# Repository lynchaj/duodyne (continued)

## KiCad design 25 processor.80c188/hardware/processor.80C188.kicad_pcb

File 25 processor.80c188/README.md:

# Duodyne 80c188 Card
80c188 processor board (hardware and software) for the Duodyne computer system.

Based on the Retrobew Computer SBC-188 board by John Coffman

## Firmware

### BIOS
 The firmware in the BIOS folder is a subset of the SBC-188 firmware.   It currently runs MS-DOS 3.3 and supports PPIDE drives on the Duodyne Disk IO card and USB drives on the Multi IO card.  It requires a RAMROM card and can be used as a primary or secondary CPU.   The RAMROM RTC is supported.
 
 UART must be jumpered for EIRQ0
 
#### BIOS ToDo:
* DiskIO Floppy Drive Support
* Missing Disk-io SD Support
* Missing Disk-io Network Support
* BIOS Support for the PCF 8584
* Better Front Panel Support
* Test multi-io serial support 
* Support for other DuoDyne Hardware
 1.Voice
 1.DualESP
 1.MappedVideo
* Support for Xenix 86
* Support for CPM 86

### Monitor
This is a simple monitor "Mon88" originally by Hans Tiggeler - http://www.ht-lab.com

### Test Programs
There are also two test roms provided.  
* Scream -- this program outputs a constant stream of "A" at 9600-n-8-1 via the on-board uart.
* Scram -- this program outputs an incrimenting character from a RAM address at 9600-n-8-1 via the on-board uart.

## Bugs 
### Hardware
   1. V 0.70
   * To get RAM access -- A21 needs to be high, and it is not. Also A20 should not be left floating.   
      1.  Connect P2 Pin 26 to U17 Pin 18.
      1.  Connect P2 Pin 28 to U17 Pin 16.
      1.  Connect RN1 Pin 3 to U17 Pin 2.
      1.  Connect RN1 Pin 5 to U17 Pin 4.
      1.  Cut Trace between U17 Pin 1 and Pin 19 (bottom of board)
      1.  Connect U17 Pin 1 U6 Pin 19

### BIOS
* Missing multi-io Mouse Support (no plans to support)
* Missing multi-io SD Support (no plans to support)

## Jumper Settings (V.90)

      JP1  - Allow RES_IN to generate board Reset
      
      JP4 - Pullups for IORQ,MREQ,WR,RD.   
            All Open for Secondary CPU
            All Shorted for only CPU

      J1 - Activation Address Port
        
      J2  - CPU Control
                1&2 Only CPU
                2&3 Secondary CPU
      
      J3  - Reset Control
                1&2 Only CPU
                2&3 Secondary CPU                
      
      J4 - Reset Switch Input
        
      J5 - Bus IRQ Enable (0-3)
                1&2 Enable Bus EIRQ3 to Int3
                3&4 Enable Bus EIRQ2 to Int2
                5&6 Enable Bus EIRQ1 to Int1
                7&8 Enable Bus EIRQ0 to Int0

      J7 i2c IRQ Selection
        
      J8 UART IRQ Selection
            (BIOS Requires INT0 - tbd)

      J13 Rom Type Selection
            1&2 32 pin Flash or CMOS 
            2&3 28 pin Flash or CMOS 
        
      J14 Rom Type Selection
            1&2 Flash (not Write Protected)
            2&3 CMOS (512K)

## BOM (V0.90)      
Qty|Reference(s)|Value
--- | ----------- | -----
33|C2, C3, C4, C5, C6, C8, C9, C10, C11, C12, C13, C14, C15, C16, C17, C18, C19, C20, C21, C22, C23, C24, C30, C31, C32, C33, C34, C35, C36, C37, C38, C39, C40|0.1u
4|C25, C26, C27, C28|10u Electrolytic
1|C29|22u Electrolytic
1|C46|47uF Electrolytic
8|D2, D5, D7, D8, D9, D10, D11, D12|LED
1|D4|LED
1|D6|1N4148
1|J1|Pin Header 02x08
1|J2|Pin Header 01x03
1|J3|Pin Header 01x03
1|J4|Pin Header 01x02
1|J7|Pin Header 02x09
1|J8|Pin Header 02x09
1|J11|Pin Header 02x20
2|J13, J14|Pin Header 01x03
1|JP1|Pin Header  01x02
1|JP4|Pin Header 02x04
3|P1, P2, P3|Pin Header 02x25
3|R1, R2, R3|10K
3|R4, R6, R7|1K
1|R5|10
1|R9|1K
3|RN1, RN4, RN5|4700  8 res network
1|RN2|10K  8 res network
1|RN3|470 8 res network
1|RN6|470 4 res network 
1|SW1|Switch:SW_Push
1|U1|74LS04
1|U2|74LS32
2|U3, U19|74ALS373
1|U4|74LS07
1|U5|8259
6|U6, U8, U10, U14, U17, U31|74LS244
1|U7|74LS240
1|U9|OSC 2x rated CPU freq (10-20mhz, should be an even number)
1|U11|74LS245
1|U12|80C188
1|U13|DS1233
2|U15, U25|GAL22V10
1|U16|74LS08
1|U18|OSC 1.8432
1|U20|TL16C550CFN
1|U21|74LS74
1|U22|74LS688
1|U23|74LS00
1|U24|74LS259
1|U26|29F040
1|U27|PCF8584
1|U28|PCF CLOCK
1|U33|74LS374

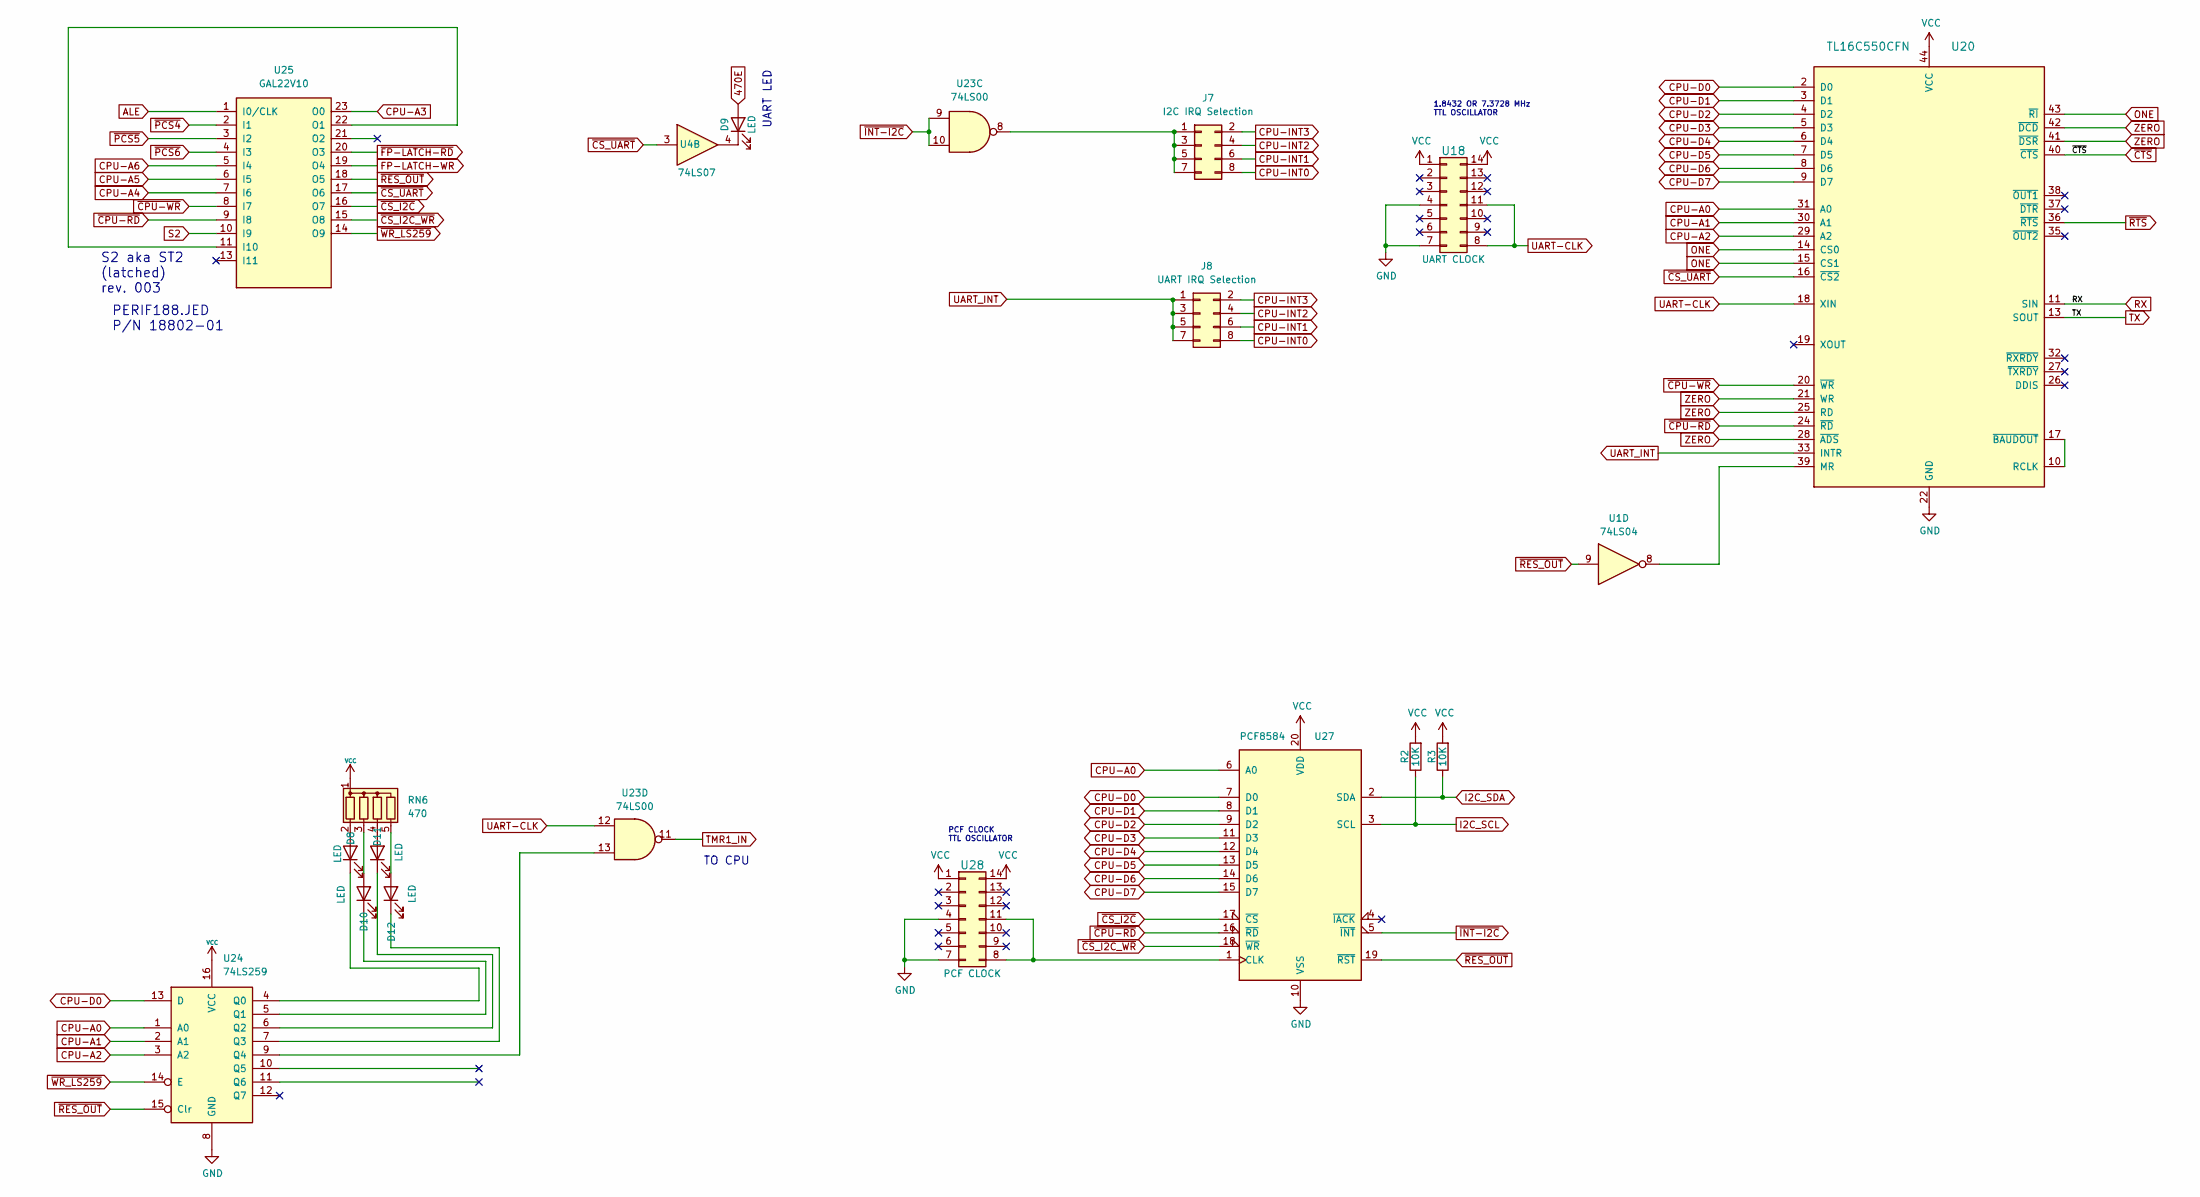
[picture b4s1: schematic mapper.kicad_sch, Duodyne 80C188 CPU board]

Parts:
D8, D9, D10, D11, D12: LED; LED_D3.0mm_Horizontal_O3.81mm_Z2.0mm
J7: I2C IRQ Selection; PinHeader_2x04_P2.54mm_Vertical
J8: UART IRQ Selection; PinHeader_2x04_P2.54mm_Vertical
R2, R3: 10K; R_Axial_DIN0207_L6.3mm_D2.5mm_P7.62mm_Horizontal
RN6: 470; R_Array_SIP5
U1: 74LS04; DIP-14_W7.62mm_Socket_LongPads
U4: 74LS07; DIP-14_W7.62mm_Socket_LongPads
U18: UART CLOCK; DIP-14_W7.62mm_Socket_LongPads
U20: TL16C550CFN; PLCC-44_THT-Socket
U23: 74LS00; DIP-14_W7.62mm_Socket_LongPads
U24: 74LS259; DIP-16_W7.62mm_Socket_LongPads
U25: GAL22V10; DIP-24_W7.62mm_Socket_LongPads
U27: PCF8584; DIP-20_W7.62mm_Socket_LongPads
U28: PCF CLOCK; DIP-14_W7.62mm_Socket_LongPads

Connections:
470E: D9.2 (A); also elsewhere on the board
ALE: U25.1 (I0/CLK); also elsewhere on the board
CPU-A0: U20.31 (A0), U24.1 (A0), U27.6 (A0); also elsewhere on the board
CPU-A1: U20.30 (A1), U24.2 (A1); also elsewhere on the board
CPU-A2: U20.29 (A2), U24.3 (A2); also elsewhere on the board
CPU-A3: U25.23 (O0); also elsewhere on the board
CPU-A4: U25.7 (I6); also elsewhere on the board
CPU-A5: U25.6 (I5); also elsewhere on the board
CPU-A6: U25.5 (I4); also elsewhere on the board
CPU-D0: U20.2 (D0), U24.13 (D), U27.7 (D0); also elsewhere on the board
CPU-D1: U20.3 (D1), U27.8 (D1); also elsewhere on the board
CPU-D2: U20.4 (D2), U27.9 (D2); also elsewhere on the board
CPU-D3: U20.5 (D3), U27.11 (D3); also elsewhere on the board
CPU-D4: U20.6 (D4), U27.12 (D4); also elsewhere on the board
CPU-D5: U20.7 (D5), U27.13 (D5); also elsewhere on the board
CPU-D6: U20.8 (D6), U27.14 (D6); also elsewhere on the board
CPU-D7: U20.9 (D7), U27.15 (D7); also elsewhere on the board
CPU-INT0: J7.8, J8.8; also elsewhere on the board
CPU-INT1: J7.6, J8.6; also elsewhere on the board
CPU-INT2: J7.4, J8.4; also elsewhere on the board
CPU-INT3: J7.2, J8.2; also elsewhere on the board
FP-LATCH-WR: U25.19 (O4); also elsewhere on the board
GND: U18.4, U18.7, U20.22 (GND), U24.8 (GND), U25.12 (GND), U27.10 (VSS), U28.4, U28.7; also elsewhere on the board
I2C_SCL: R2.1, U27.3 (SCL); also elsewhere on the board
I2C_SDA: R3.1, U27.2 (SDA); also elsewhere on the board
unnamed: D8.1 (K), U24.4 (Q0)
unnamed: D8.2 (A), RN6.2 (R1)
unnamed: D9.1 (K), U4.4
unnamed: D10.1 (K), U24.5 (Q1)
unnamed: D10.2 (A), RN6.3 (R2)
unnamed: D11.1 (K), U24.6 (Q2)
unnamed: D11.2 (A), RN6.4 (R3)
unnamed: D12.1 (K), U24.7 (Q3)
unnamed: D12.2 (A), RN6.5 (R4)
unnamed: J7.1, J7.3, J7.5, J7.7, U23.8
unnamed: U1.8, U20.39 (MR)
unnamed: U20.10 (RCLK), U20.17 (~BAUDOUT)
unnamed: U23.13, U24.9 (Q4)
unnamed: U25.11 (I10), U25.22 (O1)
unnamed: U27.1 (CLK), U28.8, U28.11
ONE: U20.14 (CS0), U20.15 (CS1), U20.43 (~RI); also elsewhere on the board
RX: U20.11 (SIN); also elsewhere on the board
S2: U25.10 (I9); also elsewhere on the board
TMR1_IN: U23.11; also elsewhere on the board
TX: U20.13 (SOUT); also elsewhere on the board
UART-CLK: U18.8, U18.11, U20.18 (XIN), U23.12
UART_INT: J8.1, J8.3, J8.5, J8.7, U20.33 (INTR)
VCC: R2.2, R3.2, RN6.1 (common), U18.1, U18.14, U20.44 (VCC), U24.16 (VCC), U25.24 (VCC), U27.20 (VDD), U28.1, U28.14; also elsewhere on the board
ZERO: U20.21 (WR), U20.25 (RD), U20.28 (~ADS), U20.41 (~DSR), U20.42 (~DCD); also elsewhere on the board
~CPU-RD: U20.24 (~RD), U25.9 (I8), U27.16 (~RD); also elsewhere on the board
~CPU-WR: U20.20 (~WR), U25.8 (I7); also elsewhere on the board
~CS_I2C_WR: U25.15 (O8), U27.18 (~WR)
~CS_I2C: U25.16 (O7), U27.17 (~CS)
~CS_UART: U4.3, U20.16 (~CS2), U25.17 (O6)
~CTS: U20.40 (~CTS); also elsewhere on the board
~FP-LATCH-RD: U25.20 (O3); also elsewhere on the board
~INT-I2C: U23.9, U23.10, U27.5 (~INT)
~PCS4: U25.2 (I1); also elsewhere on the board
~PCS5: U25.3 (I2); also elsewhere on the board
~PCS6: U25.4 (I3); also elsewhere on the board
~RES_OUT: U1.9, U24.15 (Clr), U25.18 (O5), U27.19 (~RST); also elsewhere on the board
~RTS: U20.36 (~RTS); also elsewhere on the board
~WR_LS259: U24.14 (E), U25.14 (O9)

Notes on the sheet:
PERIF188.JED P/N 18802-01
TO CPU
PCF CLOCK TTL OSCILLATOR
UART LED
S2 aka ST2 (latched) rev. 003
1.8432 OR 7.3728 MHz TTL OSCILLATOR

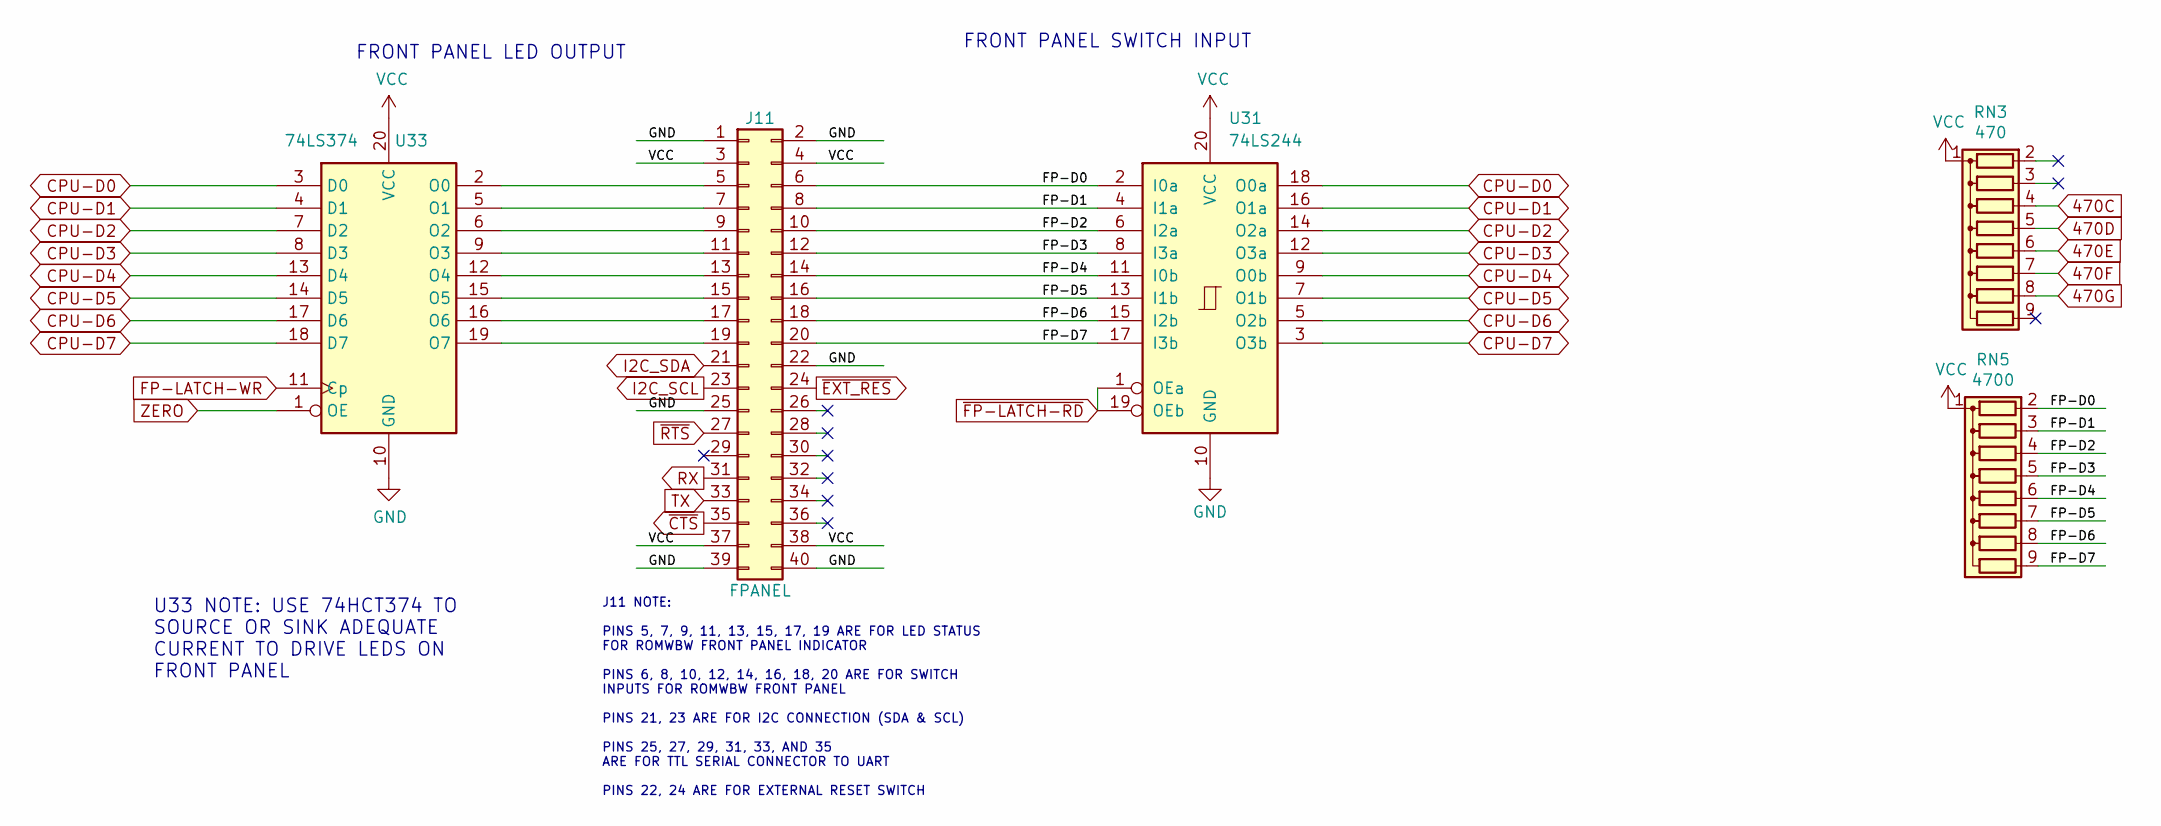
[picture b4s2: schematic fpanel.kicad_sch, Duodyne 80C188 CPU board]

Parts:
J11: FPANEL; IDC-Header_2x20_P2.54mm_Horizontal
RN3: 470; R_Array_SIP9
RN5: 4700; R_Array_SIP9
U31: 74LS244; DIP-20_W7.62mm_Socket_LongPads
U33: 74LS374; DIP-20_W7.62mm_Socket_LongPads

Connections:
470C: RN3.4 (R3); also elsewhere on the board
470D: RN3.5 (R4); also elsewhere on the board
470E: RN3.6 (R5); also elsewhere on the board
470F: RN3.7 (R6); also elsewhere on the board
470G: RN3.8 (R7); also elsewhere on the board
/fpanel/FP-D0: J11.6, RN5.2 (R1), U31.2 (I0a)
/fpanel/FP-D1: J11.8, RN5.3 (R2), U31.4 (I1a)
/fpanel/FP-D2: J11.10, RN5.4 (R3), U31.6 (I2a)
/fpanel/FP-D3: J11.12, RN5.5 (R4), U31.8 (I3a)
/fpanel/FP-D4: J11.14, RN5.6 (R5), U31.11 (I0b)
/fpanel/FP-D5: J11.16, RN5.7 (R6), U31.13 (I1b)
/fpanel/FP-D6: J11.18, RN5.8 (R7), U31.15 (I2b)
/fpanel/FP-D7: J11.20, RN5.9 (R8), U31.17 (I3b)
CPU-D0: U31.18 (O0a), U33.3 (D0); also elsewhere on the board
CPU-D1: U31.16 (O1a), U33.4 (D1); also elsewhere on the board
CPU-D2: U31.14 (O2a), U33.7 (D2); also elsewhere on the board
CPU-D3: U31.12 (O3a), U33.8 (D3); also elsewhere on the board
CPU-D4: U31.9 (O0b), U33.13 (D4); also elsewhere on the board
CPU-D5: U31.7 (O1b), U33.14 (D5); also elsewhere on the board
CPU-D6: U31.5 (O2b), U33.17 (D6); also elsewhere on the board
CPU-D7: U31.3 (O3b), U33.18 (D7); also elsewhere on the board
FP-LATCH-WR: U33.11 (Cp); also elsewhere on the board
GND: J11.1, J11.2, J11.22, J11.25, J11.39, J11.40, U31.10 (GND), U33.10 (GND); also elsewhere on the board
I2C_SCL: J11.23; also elsewhere on the board
I2C_SDA: J11.21; also elsewhere on the board
unnamed: J11.5, U33.2 (O0)
unnamed: J11.7, U33.5 (O1)
unnamed: J11.9, U33.6 (O2)
unnamed: J11.11, U33.9 (O3)
unnamed: J11.13, U33.12 (O4)
unnamed: J11.15, U33.15 (O5)
unnamed: J11.17, U33.16 (O6)
unnamed: J11.19, U33.19 (O7)
RX: J11.31; also elsewhere on the board
TX: J11.33; also elsewhere on the board
VCC: J11.3, J11.4, J11.37, J11.38, RN3.1 (common), RN5.1 (common), U31.20 (VCC), U33.20 (VCC); also elsewhere on the board
ZERO: U33.1 (OE); also elsewhere on the board
~CTS: J11.35; also elsewhere on the board
~EXT_RES: J11.24; also elsewhere on the board
~FP-LATCH-RD: U31.1 (OEa), U31.19 (OEb); also elsewhere on the board
~RTS: J11.27; also elsewhere on the board

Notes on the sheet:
J11 NOTE: PINS 5, 7, 9, 11, 13, 15, 17, 19 ARE FOR LED STATUS FOR ROMWBW FRONT PANEL INDICATOR PINS 6, 8, 10, 12, 14, 16, 18, 20 ARE FOR SWITCH INPUTS FOR ROMWBW FRONT PANEL PINS 21, 23 ARE FOR I2C CONNECTION (SDA & SCL) PINS 25, 27, 29, 31, 33, AND 35 ARE FOR TTL SERIAL CONNECTOR TO UART PINS 22, 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
U33 NOTE: USE 74HCT374 TO SOURCE OR SINK ADEQUATE CURRENT TO DRIVE LEDS ON FRONT PANEL
FRONT PANEL SWITCH INPUT
FRONT PANEL LED OUTPUT

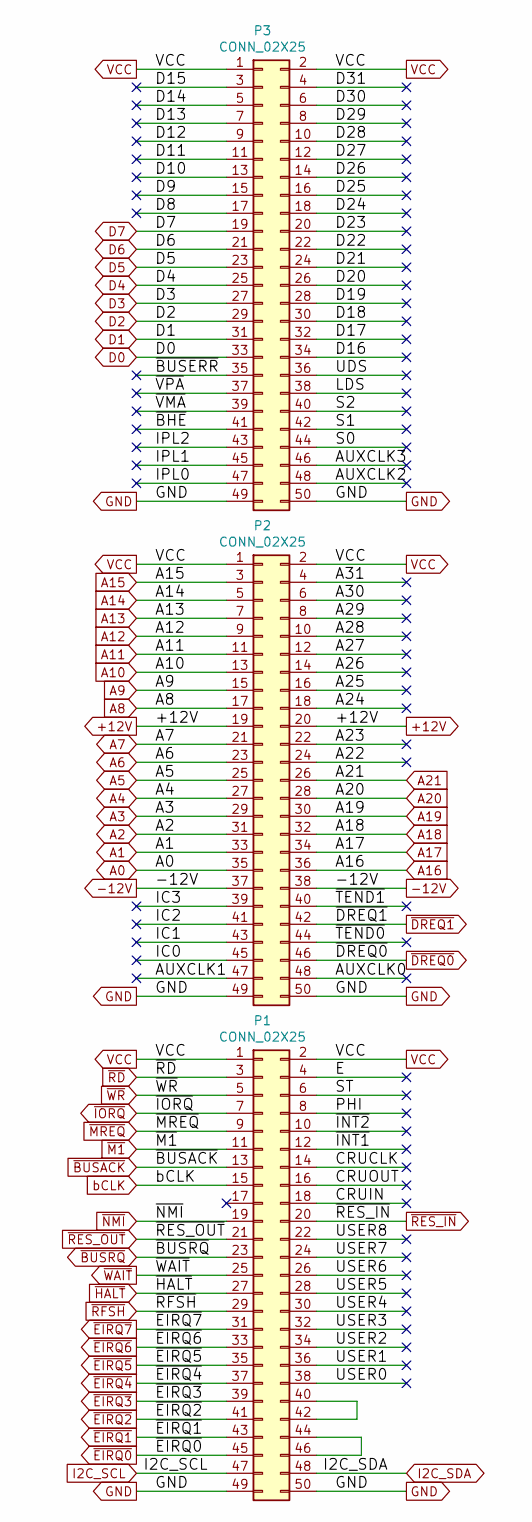
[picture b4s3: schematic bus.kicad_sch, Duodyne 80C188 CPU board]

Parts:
P1, P2, P3: CONN_02X25; IDC-Header_2x25_P2.54mm_Horizontal

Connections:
+12V: P2.19, P2.20
-12V: P2.37, P2.38
/bus/A22: P2.24
/bus/A23: P2.22
/bus/A24: P2.18
/bus/A25: P2.16
/bus/A26: P2.14
/bus/A27: P2.12
/bus/A28: P2.10
/bus/A29: P2.8
/bus/A30: P2.6
/bus/A31: P2.4
/bus/AUXCLK0: P2.48
/bus/AUXCLK1: P2.47
/bus/AUXCLK2: P3.48
/bus/AUXCLK3: P3.46
/bus/CRUCLK: P1.14
/bus/CRUIN: P1.18
/bus/CRUOUT: P1.16
/bus/D8: P3.17
/bus/D9: P3.15
/bus/D10: P3.13
/bus/D11: P3.11
/bus/D12: P3.9
/bus/D13: P3.7
/bus/D14: P3.5
/bus/D15: P3.3
/bus/D16: P3.34
/bus/D17: P3.32
/bus/D18: P3.30
/bus/D19: P3.28
/bus/D20: P3.26
/bus/D21: P3.24
/bus/D22: P3.22
/bus/D23: P3.20
/bus/D24: P3.18
/bus/D25: P3.16
/bus/D26: P3.14
/bus/D27: P3.12
/bus/D28: P3.10
/bus/D29: P3.8
/bus/D30: P3.6
/bus/D31: P3.4
/bus/E: P1.4
/bus/IC0: P2.45
/bus/IC1: P2.43
/bus/IC2: P2.41
/bus/IC3: P2.39
/bus/IPL0: P3.47
/bus/IPL1: P3.45
/bus/IPL2: P3.43
/bus/LDS: P3.38
/bus/PHI: P1.8
/bus/S0: P3.44
/bus/S1: P3.42
/bus/S2: P3.40
/bus/ST: P1.6
/bus/UDS: P3.36
/bus/USER0: P1.38
/bus/USER1: P1.36
/bus/USER2: P1.34
/bus/USER3: P1.32
/bus/USER4: P1.30
/bus/USER5: P1.28
/bus/USER6: P1.26
/bus/USER7: P1.24
/bus/USER8: P1.22
/bus/~BHE: P3.41
/bus/~BUSERR: P3.35
/bus/~INT1: P1.12
/bus/~INT2: P1.10
/bus/~TEND0: P2.44
/bus/~TEND1: P2.40
/bus/~VMA: P3.39
/bus/~VPA: P3.37
A0: P2.35; also elsewhere on the board
A1: P2.33; also elsewhere on the board
A2: P2.31; also elsewhere on the board
A3: P2.29; also elsewhere on the board
A4: P2.27; also elsewhere on the board
A5: P2.25; also elsewhere on the board
A6: P2.23; also elsewhere on the board
A7: P2.21; also elsewhere on the board
A8: P2.17; also elsewhere on the board
A9: P2.15; also elsewhere on the board
A10: P2.13; also elsewhere on the board
A11: P2.11; also elsewhere on the board
A12: P2.9; also elsewhere on the board
A13: P2.7; also elsewhere on the board
A14: P2.5; also elsewhere on the board
A15: P2.3; also elsewhere on the board
A16: P2.36; also elsewhere on the board
A17: P2.34; also elsewhere on the board
A18: P2.32; also elsewhere on the board
A19: P2.30; also elsewhere on the board
A20: P2.28; also elsewhere on the board
A21: P2.26; also elsewhere on the board
D0: P3.33; also elsewhere on the board
D1: P3.31; also elsewhere on the board
D2: P3.29; also elsewhere on the board
D3: P3.27; also elsewhere on the board
D4: P3.25; also elsewhere on the board
D5: P3.23; also elsewhere on the board
D6: P3.21; also elsewhere on the board
D7: P3.19; also elsewhere on the board
GND: P1.49, P1.50, P2.49, P2.50, P3.49, P3.50; also elsewhere on the board
I2C_SCL: P1.47; also elsewhere on the board
I2C_SDA: P1.48; also elsewhere on the board
unnamed: P1.40, P1.42
unnamed: P1.44, P1.46
VCC: P1.1, P1.2, P2.1, P2.2, P3.1, P3.2; also elsewhere on the board
bCLK: P1.15; also elsewhere on the board
~BUSACK: P1.13; also elsewhere on the board
~BUSRQ: P1.23; also elsewhere on the board
~DREQ0: P2.46; also elsewhere on the board
~DREQ1: P2.42; also elsewhere on the board
~EIRQ0: P1.45; also elsewhere on the board
~EIRQ1: P1.43; also elsewhere on the board
~EIRQ2: P1.41; also elsewhere on the board
~EIRQ3: P1.39; also elsewhere on the board
~EIRQ4: P1.37; also elsewhere on the board
~EIRQ5: P1.35; also elsewhere on the board
~EIRQ6: P1.33; also elsewhere on the board
~EIRQ7: P1.31; also elsewhere on the board
~HALT: P1.27; also elsewhere on the board
~IORQ: P1.7; also elsewhere on the board
~M1: P1.11; also elsewhere on the board
~MREQ: P1.9; also elsewhere on the board
~NMI: P1.19; also elsewhere on the board
~RD: P1.3; also elsewhere on the board
~RES_IN: P1.20; also elsewhere on the board
~RES_OUT: P1.21; also elsewhere on the board
~RFSH: P1.29; also elsewhere on the board
~WAIT: P1.25; also elsewhere on the board
~WR: P1.5; also elsewhere on the board

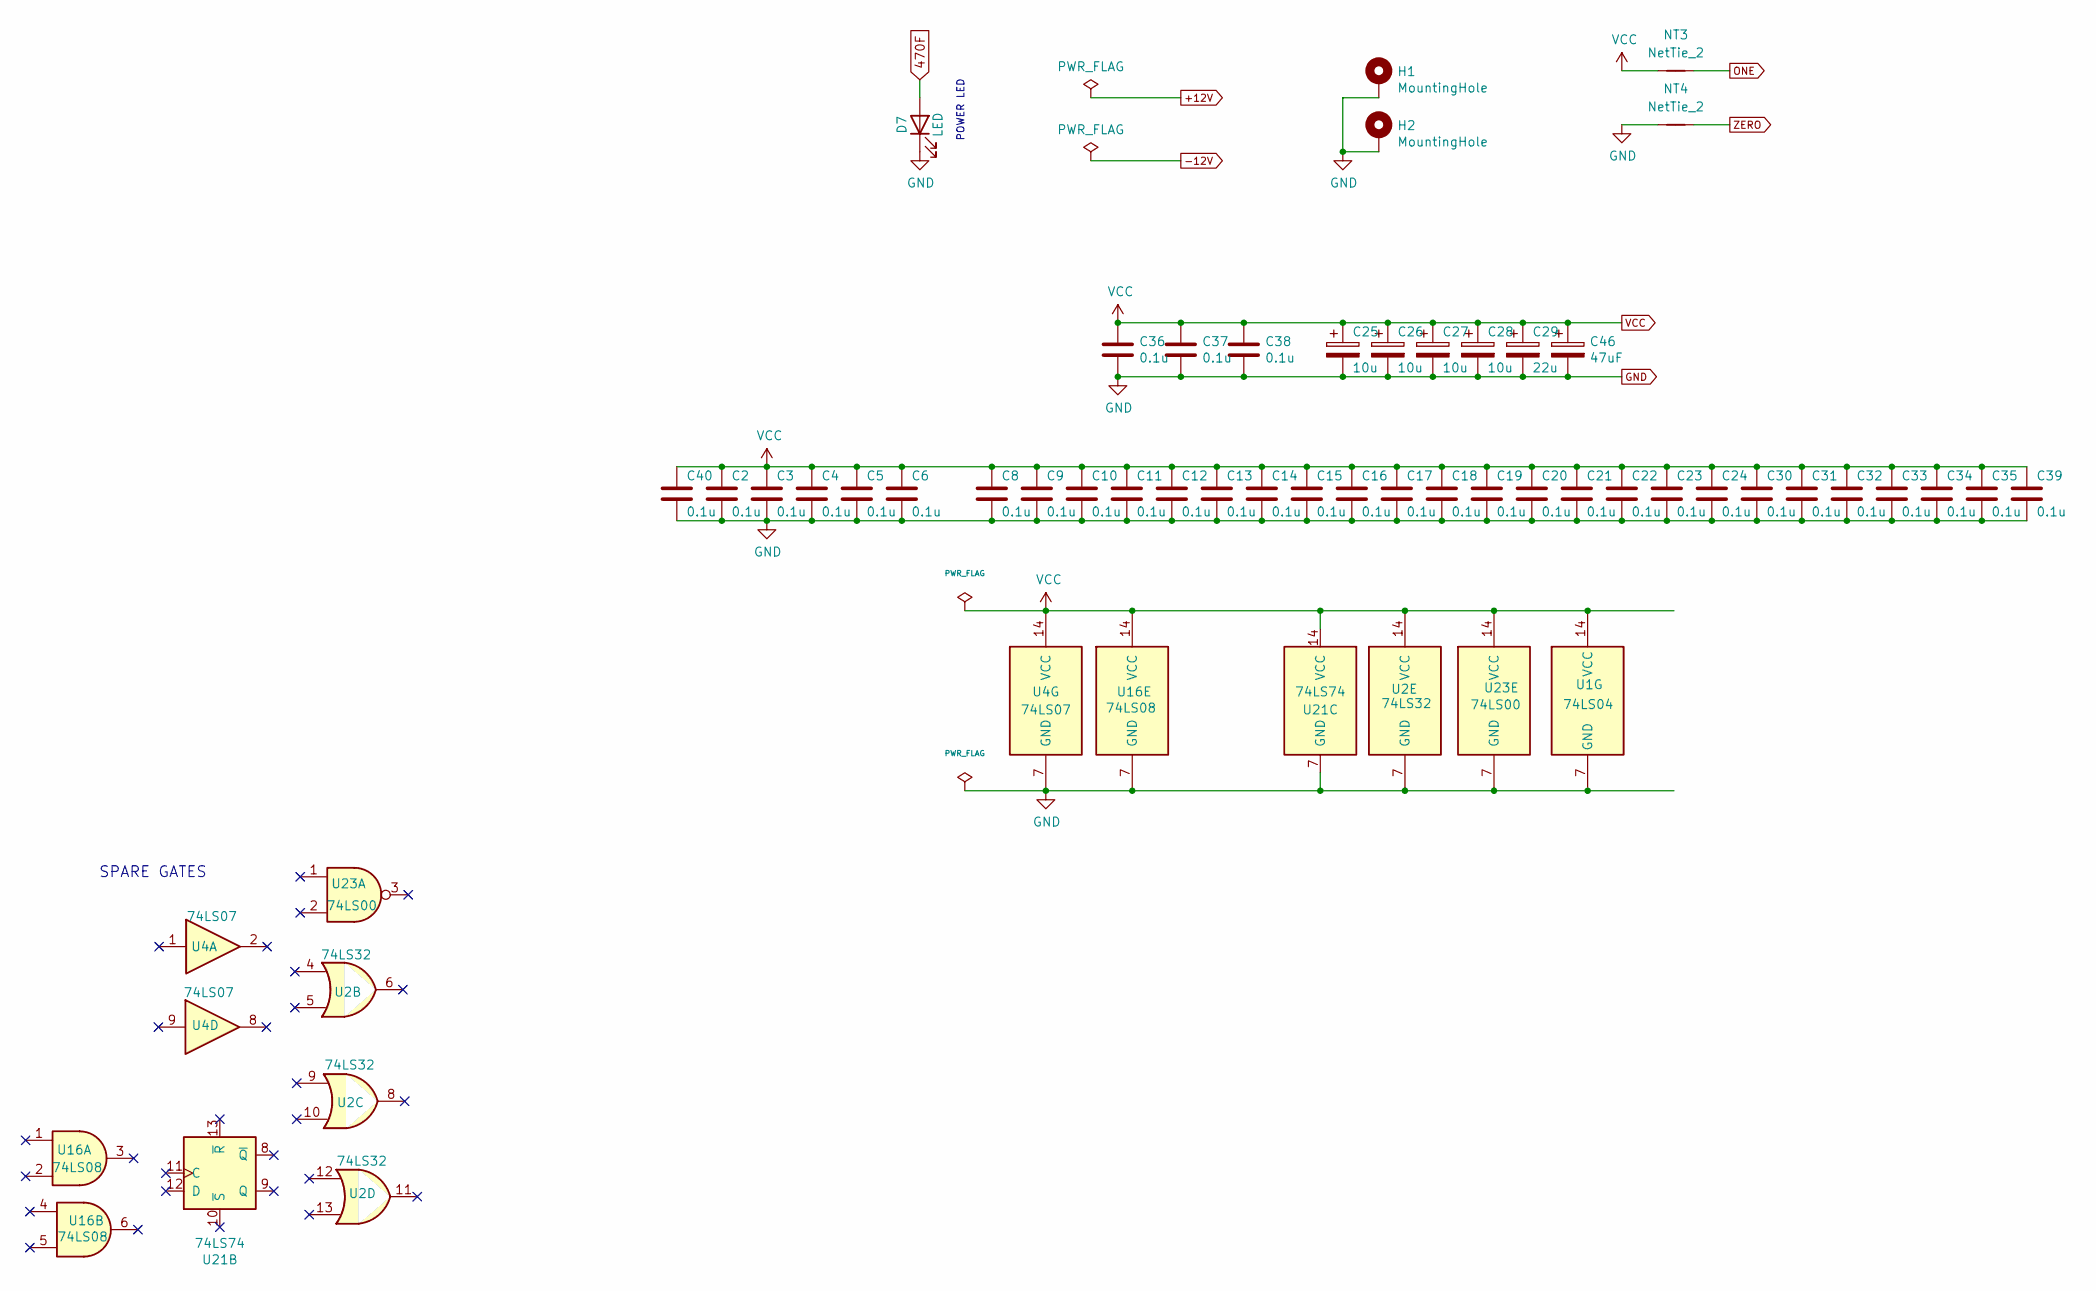
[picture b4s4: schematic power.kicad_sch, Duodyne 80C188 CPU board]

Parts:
C2, C3, C4, C5, C6, C8, C9, C10, C11, C12, C13, C14, C15, C16, C17, C18, C19, C20, C21, C22, C23, C24, C30, C31, C32, C33, C34, C35, C36, C37, C38, C39, C40: 0.1u; C_Disc_D5.0mm_W2.5mm_P5.00mm
C25, C26, C27, C28: 10u; CP_Radial_D5.0mm_P2.50mm
C29: 22u; CP_Radial_D5.0mm_P2.50mm
C46: 47uF; CP_Radial_D5.0mm_P2.50mm
D7: LED; LED_D3.0mm_Horizontal_O3.81mm_Z2.0mm
H1, H2: MountingHole; MountingHole_3.2mm_M3_Pad
NT3, NT4: NetTie_2; NetTie-2_THT_Pad0.3mm
U1: 74LS04; DIP-14_W7.62mm_Socket_LongPads
U2: 74LS32; DIP-14_W7.62mm_Socket_LongPads
U4: 74LS07; DIP-14_W7.62mm_Socket_LongPads
U16: 74LS08; DIP-14_W7.62mm_Socket_LongPads
U21: 74LS74; DIP-14_W7.62mm_Socket_LongPads
U23: 74LS00; DIP-14_W7.62mm_Socket_LongPads

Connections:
470F: D7.2 (A); also elsewhere on the board
GND: C2.2, C3.2, C4.2, C5.2, C6.2, C8.2, C9.2, C10.2, C11.2, C12.2, C13.2, C14.2, C15.2, C16.2, C17.2, C18.2, C19.2, C20.2, C21.2, C22.2, C23.2, C24.2, C25.2, C26.2, C27.2, C28.2, C29.2, C30.2, C31.2, C32.2, C33.2, C34.2, C35.2, C36.2, C37.2, C38.2, C39.2, C40.2, C46.2, D7.1 (K), H1.1, H2.1, NT4.1, U1.7 (GND), U2.7 (GND), U4.7 (GND), U16.7 (GND), U21.7 (GND), U23.7 (GND); also elsewhere on the board
ONE: NT3.2; also elsewhere on the board
VCC: C2.1, C3.1, C4.1, C5.1, C6.1, C8.1, C9.1, C10.1, C11.1, C12.1, C13.1, C14.1, C15.1, C16.1, C17.1, C18.1, C19.1, C20.1, C21.1, C22.1, C23.1, C24.1, C25.1, C26.1, C27.1, C28.1, C29.1, C30.1, C31.1, C32.1, C33.1, C34.1, C35.1, C36.1, C37.1, C38.1, C39.1, C40.1, C46.1, NT3.1, U1.14 (VCC), U2.14 (VCC), U4.14 (VCC), U16.14 (VCC), U21.14 (VCC), U23.14 (VCC); also elsewhere on the board
ZERO: NT4.2; also elsewhere on the board

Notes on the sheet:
POWER LED
SPARE GATES
